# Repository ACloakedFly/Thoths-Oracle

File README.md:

# Thoth's Oracle
## Table of Contents:
- [Features](#Features)
- [Make your own](#Make-your-own)
- [How it works](#How-it-works)
  - [Hardware](#Hardware)
  - [Software](#Software)
  - [Firmware](#Firmware)
- [Configuration](#Configuration)
- [FAQ](#FAQ)
- [Installation](#Installation)
  - [Windows](#Windows)
    - [Launch on startup](#Windows-launch-on-startup)
  - [Linux](#Linux-Tested-on-Ubuntu)
    - [Example](#Example)
    - [GNOME Specific](#GNOME-Specific)
    - [Linux launch on startup](#Linux-launch-on-startup)
    - [Phone Connection](#Phone-connection-to-linux)
- [License](#License)

### USB operated media display/controller for Windows, Linux(, MacOS WIP).

USB music display helps you keep track of what you are listening to without taking up precious screen space. Thoth's Oracle provides a one stop shop for checking on the current media information and basic controls such as skipping tracks, playing and pausing and adjusting the volume.

# Features:

- Software agnostic companion app listens to operating system rather than a specific program like Spotify app or Firefox
  - If OS is aware of media, companion app will be as well
- 320x480 IPS display for maximum readability
- Display the available metadata of current media
  - Thumbnail
  - Title
  - Album
  - Artist
  - Duration and current position
- Basic media control
  - Play/pause
  - Skip track
  - Previous track
  - Mute/unmute
  - Volume control
- Tiltable screen
- Brightness control
- Lightweight companion app (peak RAM usage <80MB, avg <50MB)
- Wallpaper mode to cycle through local images in Wallpaper folder
- Standard components allowing for custom configuration and ease of assembly
  - Hotswappable MX style or Kailh Choc low-profile style switches
  - 6mm rotary potentiometer and encoder
  - 3D printed shell
  - One screw size
  - Small PCB with mostly THT components. Only the hotswap sockets are SMD (hand solderable)

# Make your own!

Everything you need to make your own should be in BOM-and-Assembly. Let me know if anything can be improved.

# How it works:

## Hardware:

- An ESP32-S3 zero controls all of the device inputs and displays information on screen
- ESP32 communicates with PC over USB C OTG connection

## Software:

- The software is written in C# for the Windows App.
- Companion app catches changes to focused media broadcast from the operating system.
- On media change, Thoth requests metadata, packages it, then waits for signal from the Oracle that it is ready to receive the data.
- Metadata is packaged as follows with header tag denoting type, size, etc.:
  - System information containing date and time
  - Media duration and position
  - Media text: title, album, artist
  - Thumbnail
- All text is converted to UTF-8.
- Once ready signal is received, Thoth sends a package over serial port, waits for ready signal, then proceeds to next package.
- When input commands are received, Thoth requests the OS completes the action.

## Firmware:

- The firmware is written in C.
- All serial communications are handled by Core 1. Core 0 handles all display features running LVGL.
- Thoth's Oracle emits ready signal periodically while idling, and emits control commands as soon as they are inputted by the user.
- When data is received, the header tag is analyzed to know which buffer it should be put in.
- If there is an error with the header tag, all subsequent data is dumped, and firmware waits for a pause in data transmission before resetting header information and buffers, and returning to idle state.
- If no errors are detected, data is placed directly into the correct buffer for further analysis in the case of text data, or displayed immediately for images (rolling effect as image loads).
- Media text starts as one big array of characters, and is split into the three fields using escape characters inserted by companion app.
- The font used is DejaVu-Sans in 16 point, with as much of the character set as is hopefully reasonable to ensure maximum language compatibility, without containing the entire set.
- Once the expected number of bytes is received based on the header tag, the header is reset, Oracle emits a ready signal, then enters idle state.
- If firmware times out before receiving expected data, header tag is reset and device enters idle state.

# Configuration:

 The following can be configured from companion app or config file
- Which program to listen to
- Port the device is connected to
- Sensitivity of volume knob
- Which output device to control (default, speakers, headphones, etc.)
- Wallpaper mode

# FAQ:

Someone ask me something, please.

# Installation:

### Windows:

Companion app is provided as portable application that doesn't need installation. Just download and extract the software file for your system wherever you want and run it!

#### Windows launch on startup:
- Right click on .exe and select 'Create shortcut'
- Copy the shortcut to %APPDATA%\Microsoft\Windows\Start Menu\Programs\Startup

### Linux (Tested on Ubuntu):

- Extract folder to desired location.
- Edit .desktop file to match new location if you want app to appear in Apps list.
- Validate and install
```
desktop-file-validate thoths_oracle.desktop
desktop-file-install thoths_oracle.desktop
```
- Check which port Oracle is connected to. It should show up as USB ACM device.
- Verify the device's group permissions are rw and note the group.
- Verify you are part of the group.
- Reboot
#### Example:

```
$ sudo dmesg | grep tty
[    0.139832] printk: legacy console [tty0] enabled
[    6.652489] cdc_acm 1-5.2.2:1.0: ttyACM0: USB ACM device
$ sudo chmod g+rw /dev/ttyACM0
$ ls -ld /dev/ttyACM0
crw-rw---- 1 root dialout 166, 0 Dec  2 18:21 /dev/ttyACM0
$ sudo usermod -a -G dialout dominique
$ sudo reboot
```
#### GNOME Specific:
GNOME may need an extension such as [AppIndicator and KStatusNotifierItem Support](https://extensions.gnome.org/extension/615/appindicator-support/) to display the menu along the top panel. Otherwise, the program will run normally but all settings will have to be changed through the configuration file.

#### Linux launch on startup:
Using Startup Applications Preferences:
-  Add a new entry named Thoths Oracle.
-  If you have installed the .desktop file, set the command to gtk-launch thoths_oracle.desktop
-  Otherwise, change the command to the location you extracted Thoth's Oracle in.
    - eg. /home/dominique/Documents/Programs/Thoths_Oracle_linux/Thoths_Oracle
- Add a comment if desired and save.

#### Phone connection to Linux:
To use audio from phone with all the same features, install [GSConnect](https://github.com/GSConnect/gnome-shell-extension-gsconnect/wiki) for GNOME, or [KDE Connect](https://kdeconnect.kde.org/) for KDE Plasma and follow the instructions to set it up.  
Add kdeconnect or gsconnect to config.yaml in MonitoredProgram section.  
Next, connect phone (source) to Linux (sink) through bluetooth for audio.  
Done!  

# License:

Thoth's Oracle is licensed under GPL-3.0

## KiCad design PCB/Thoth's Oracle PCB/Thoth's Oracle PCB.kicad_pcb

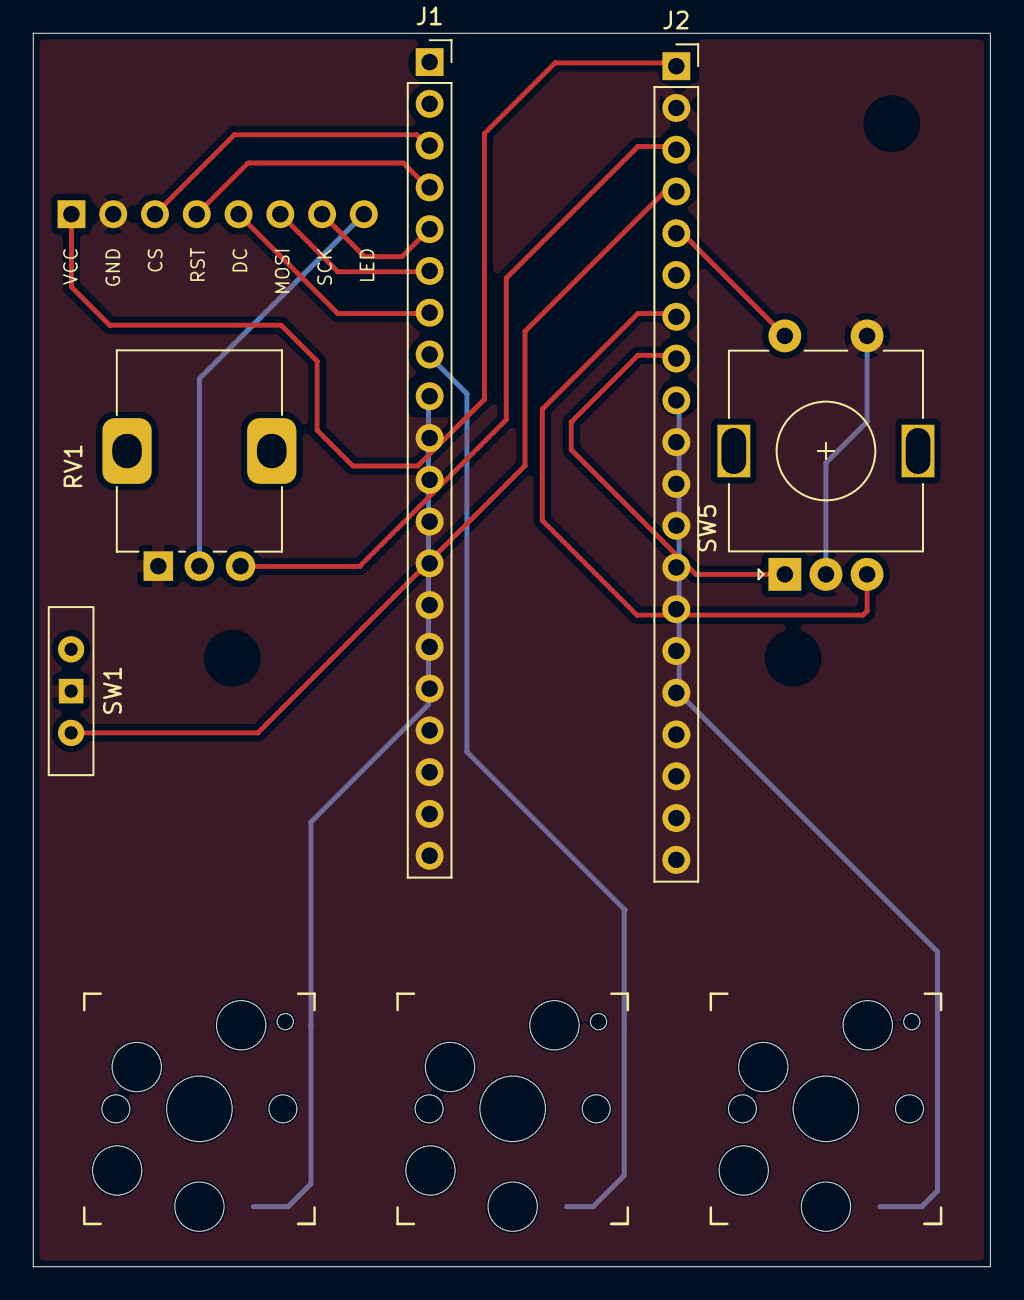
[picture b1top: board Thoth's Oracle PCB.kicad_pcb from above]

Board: 2 copper layers, 58.2 x 75.0 mm, 12 parts (1 on the bottom side), 14 nets.

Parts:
J1: Nano_5v; PinSocket_1x20_P2.54mm_Vertical
J2: Nano_3v3; PinSocket_1x20_P2.54mm_Vertical
J3: Display; PinSocket_1x08_P2.54mm_Horizontal
RV1: R_Potentiometer; Potentiometer_Alps_RK09K_Single_Vertical
SW1: Orientation; SW_Slide-03_Wuerth-WS-SLTV_10x2.5x6.4_P2.54mm
SW2: Prev; Kailh_socket_MX_modified
SW3: Play/Pause; Kailh_socket_MX_modified
SW4: Next; Kailh_socket_MX_modified
SW5: RotaryEncoder_Switch; RotaryEncoder_Alps_EC11E-Switch_Vertical_H20mm
SW6: PP_Alt; Kailh_socket_PG1350_modified
SW7: Prev_Alt; Kailh_socket_PG1350_modified
SW8: Next_Alt; Kailh_socket_PG1350_modified

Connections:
3v3: J1.7, RV1.3
GND: J1.8, J3.2, RV1.1, SW1.1 (B), SW2.2, SW3.2, SW4.2, SW5.C, SW5.S1, SW6.2, SW7.2, SW8.2
LED: J3.8, RV1.2
P1: J1.6, SW1.2 (C)
P2: J1.3, J1.5, SW5.S2
P5: J1.2, SW5.A
P6: J1.1, SW4.1, SW8.1
P7: J2.1, SW2.1, SW7.1
P8: J2.2, SW3.1, SW6.1
P9: J2.3, J3.5
P10: J2.4, J3.6
P11: J2.5, J3.7
P12: J2.6, J3.4
P13: J2.7, J3.3

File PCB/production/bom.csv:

Designator,Footprint,Quantity,Value,LCSC Part #
J1,PinSocket_1x09_P2.54mm_Vertical,1,IO,
J2,PinSocket_1x09_P2.54mm_Vertical,1,MCUDisplay,
J3,PinSocket_1x08_P2.54mm_Vertical,1,Display,
RV1,Potentiometer_Alps_RK09K_Single_Vertical,1,R_Potentiometer,
SW1,SW_Slide-03_Wuerth-WS-SLTV_10x2.5x6.4_P2.54mm,1,Orientation,
SW2,Kailh_socket_MX_PG1350,1,Prev,
SW3,Kailh_socket_MX_PG1350,1,Play/Pause,
SW4,Kailh_socket_MX_PG1350,1,Next,
SW5,RotaryEncoder_Alps_EC11E-Switch_Vertical_H20mm,1,RotaryEncoder_Switch,

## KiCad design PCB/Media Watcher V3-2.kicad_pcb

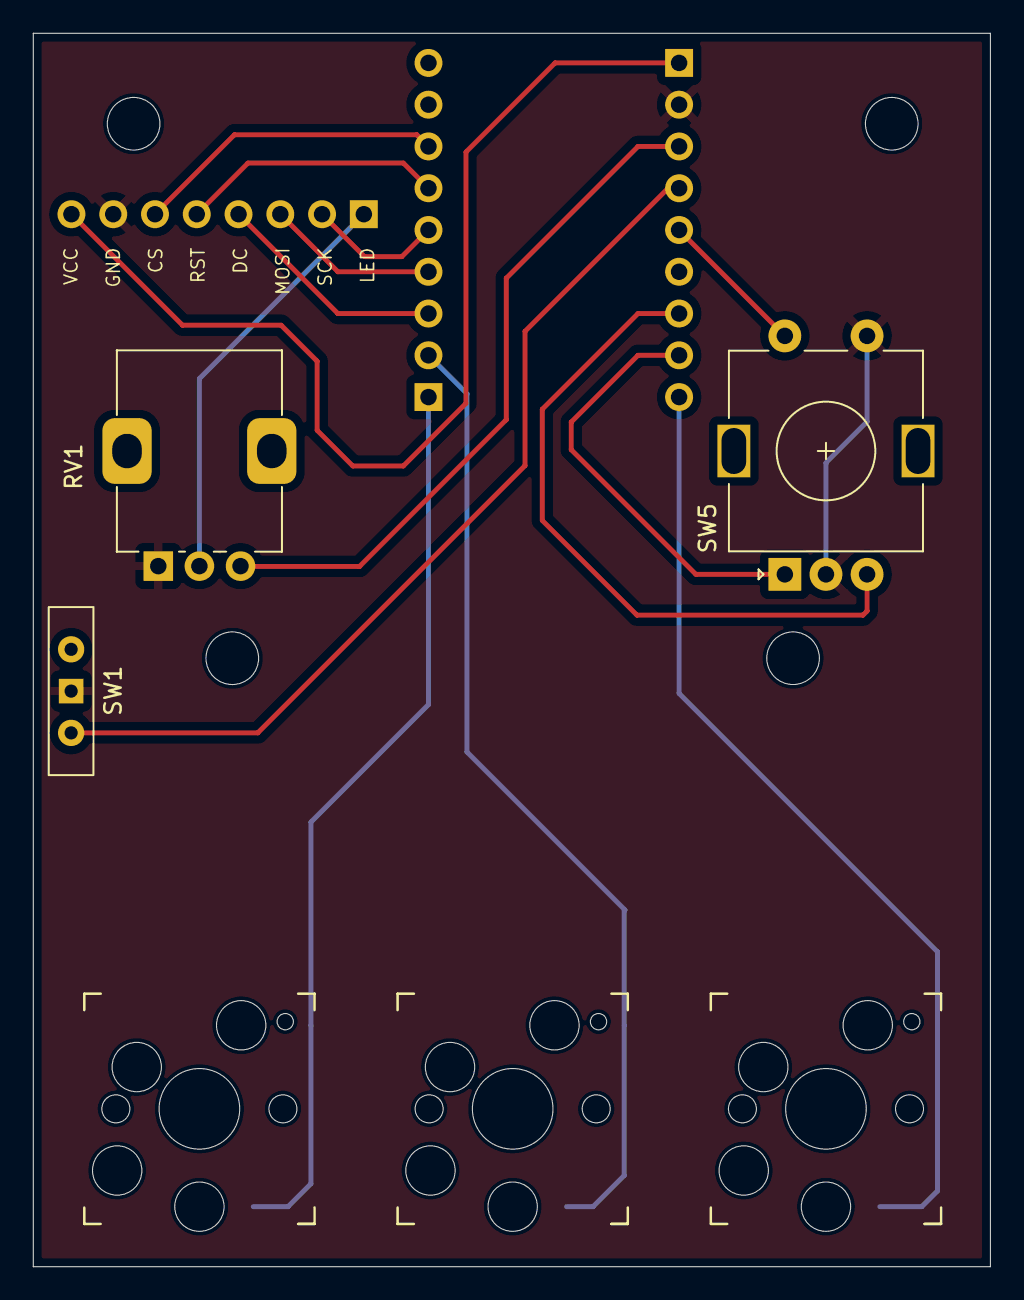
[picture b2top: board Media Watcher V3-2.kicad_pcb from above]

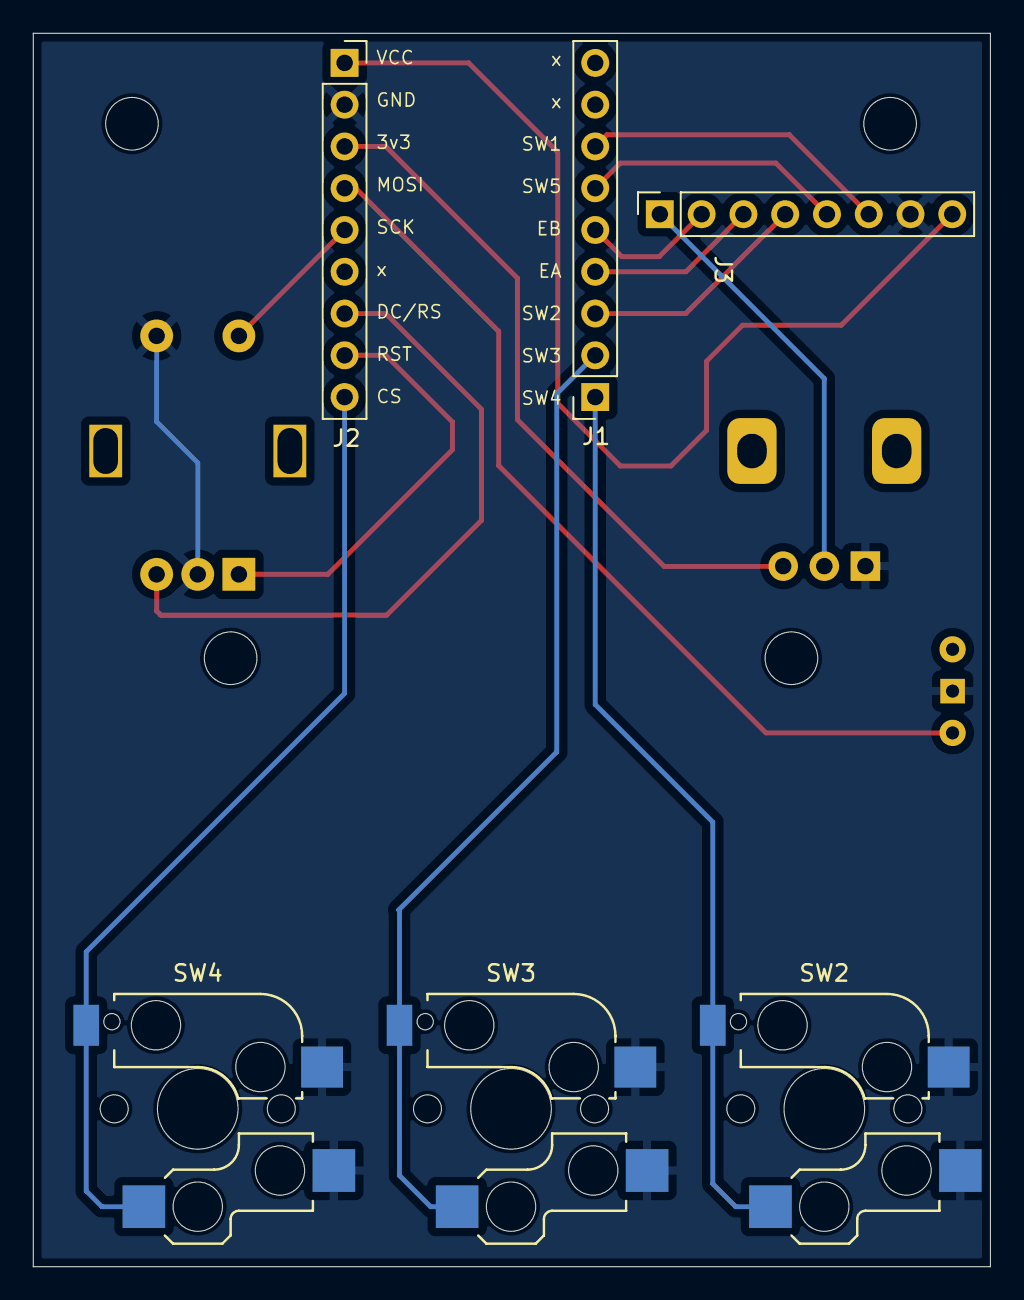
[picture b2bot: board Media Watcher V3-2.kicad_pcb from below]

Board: 2 copper layers, 58.2 x 75.0 mm, 9 parts (3 on the bottom side), 16 nets.

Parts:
J1: IO; PinSocket_1x09_P2.54mm_Vertical
J2: MCUDisplay; PinSocket_1x09_P2.54mm_Vertical
J3: Display; PinSocket_1x08_P2.54mm_Vertical
RV1: R_Potentiometer; Potentiometer_Alps_RK09K_Single_Vertical
SW1: Orientation; SW_Slide-03_Wuerth-WS-SLTV_10x2.5x6.4_P2.54mm
SW2: Prev; Kailh_socket_MX_PG1350
SW3: Play/Pause; Kailh_socket_MX_PG1350
SW4: Next; Kailh_socket_MX_PG1350
SW5: RotaryEncoder_Switch; RotaryEncoder_Alps_EC11E-Switch_Vertical_H20mm

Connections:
3v3: J2.3, RV1.3
+5V: J2.1, J3.8
GND: J2.2, J3.7, RV1.1, SW1.1 (B), SW2.2, SW3.2, SW4.2, SW5.C, SW5.S1
LED: J3.1, RV1.2
P1: J2.4, SW1.2 (C)
P2: J2.5, SW5.S2
P4: J2.7, SW5.B
P5: J2.8, SW5.A
P6: J2.9, SW4.1
P7: J1.1, SW2.1
P8: J1.2, SW3.1
P9: J1.3, J3.4
P10: J1.4, J3.3
P11: J1.5, J3.2
P12: J1.6, J3.5
P13: J1.7, J3.6

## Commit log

2025-07-03 Inital
2025-07-03 Initial 1
2025-07-04 Restructure
2025-07-09 Added PCB and 3d models
2025-07-09 Rename PCB Assembly Instructions.md to README.md
2025-07-09 Rename README to README.md
2025-07-09 Added Software
2025-07-11 Big updates
2025-07-13 Added documentation
2025-07-13 Finished documentation and cleaned up code
2025-07-13 Added firmware README
2025-07-14 Further cleaning
2025-07-14 Cleaning
2025-07-16 Changed messages to separate idling and finished
2025-07-16 Cleaned up code Added YAML file Proper connect/reconnect/disconnect behaviour
2025-07-16 Added classes for communication codes
2025-07-16 UI works with serial comms
2025-07-16 Adding configuration support
2025-07-16 More config stuff
2025-07-16 Added Timers for DeviceHandler loop
2025-07-17 Cleaned up UI
2025-07-18 Finaliozed
2025-07-18 Smol
2025-07-18 untracked builds folder
2025-07-18 Untracked builds/ folder
2025-07-18 Lgos and icons
2025-07-19 Customized UI
2025-07-20 Finalized Software
2025-07-20 Finalized
2025-07-20 Fixed GSMTCS bug on initial connection without a config file
2025-07-20 Increased default mediacheck time for better responsiveness
2025-07-20 Reintroduced delay between retrieving thumbnail and resizing to ensure it is updated before resizing
2025-07-20 Preparing for release
2025-07-20 Added image of Oracle
2025-07-20 Added image of the Oracle
2025-07-22 Cleaned new declarations
2025-07-23 Added priority to MonitoredProgram and moved it to sessionschanged rather than currentsessionchanged. Updated config to reflect this. Added copyright and version number to exe. If program is firefox,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
2025-07-23 Tiny cleanup
2025-07-23 Added retry if image has not been received yet instead of just returning unsuccessfully
2025-07-24 Added product images
2025-07-24 Cleaned board
2025-07-24 Cleaned shell
2025-07-24 Rename BOM.md to BOM-and-Assembly.md
2025-07-24 Cleaned stl
2025-07-24 Fixed thumbscrew orientation
2025-07-24 Added support setting
2025-07-25 Added queue for media writing thread to let other threads send messages. Fixed a problem with the default config causing errors on first startup
2025-07-25 Removed unnecessary using
2025-07-26 Reworked Reading and removed a bunch of async calls Fixed configuration files not loading correctly
2025-07-26 Fixed issues with config
2025-07-27 Added build pictures and updated inputs plate
2025-07-27 Added a couple more Assembly_Pics
2025-07-28 Removed some metadata from images
2025-08-08 Separated hotswap sockets with modified footprints so they don't overlap. Typo in assembly
2025-09-16 Configuration file fixed to actually update correct values and not the non-ui from ui csproj updated for true single file publishing
2025-09-16 added more characters
2025-09-18 Added better support for Windows 11
2025-09-30 Added flag to check duration, if duration set, only update play status
2025-10-10 Moved windows software files into dedicated folder in perparation of other operating systems
2025-10-10 Added linux Software
2025-10-10 Fixed some possible null dereferences and icon file path Updated to Windows 11 .net8.0 minimum target, still works on Windows 10
2025-10-15 Added ui and added licence
2025-10-15 Added spec and example desktop file
2025-12-02 Update README.md
    Added installation instructions for Linux (Ubuntu)
2025-12-02 Update README.md
    Added startup launch instructions
2025-12-08 Added LittleFS
2025-12-11 Testing new gif feature
2025-12-14 Update README.md
    typo
2026-01-05 Fix for Windows losing connection when asleep or off
2026-01-05 Upgraded Magick.Net version to latest patch
2026-01-09 Stableish gif!
2026-01-10 Seems to work with octal flash chip with minimal tearing
2026-01-11 Updated requirements
2026-01-13 Fixed the last fix for handling sleep. Last attempt incorrectly used the serial exception handler. New fix uses the mediacheck function to repoll the current media session. Also fixed bug with the co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
2026-01-13 Small fixes for initial config handling
2026-01-21 Added more context to input logging, added automatically checking for icons in parent folder rather than changing between testing and "production", Removide subdirectory checking in ConfigHandler, th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
2026-01-22 Added spam protection on config changes App now warns if selected device is not found Fixed small issue with Default Device seemingly being selected if selected device is not found (until something i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
2026-01-22 Now checks if currently selected playback device is default when config set to Default Device. If not default, get new default.
2026-01-22 Updated csproj for easier publishing
2026-02-03 Updated time handling for proper time
2026-02-04 Only makes time on minute change rather than every second which was causing time drift
2026-02-09 Added exception hanlder to inputs from device Tweaked default config to have common apps watched by default
2026-02-16 Big changes to linux. Increased stability, added automatic session handling, fixed occasional playback status not being updated
2026-02-16 Updated requirements.txt
2026-02-16 Added shortcut to folder for ease of use Added x11 as backend in .desktop file because it seems to not work otherwise Refactored session watching. It could probably use more work to simplify it, but 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
2026-02-16 Update README.md
    Updated startup command instructions for linux
2026-02-18 Added live colour changing to Firmware Added very basic colour changing in Linux software. Right now it is just through the config file, but the plan is a colour picker in the tray icon. This doesn't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
2026-02-22 Fixed sleep causing infinite loop of writing to disk (very not cool) Added file size check to log to not exceed MAX_LOG_SIZE (set to 200 mb for now, probably way too big for production, but good for 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
2026-02-26 More stability improvements, reworked uri handling
2026-03-15 Added better mpris:artUrl handling
2026-03-15 Reduced max log file size to 20 mb
2026-03-16 Added disconnect and reconnect handling. Tweaked media check
2026-03-16 Updated exit handling. Much less hanging around past its welcome.
2026-03-16 Wait do I even need to join every thread?
2026-04-12 Update README.md
    Added TOC, basic instructions for bluetooth audio
2026-05-05 many things changed a while ago
2026-05-08 Working on gif capabilites with 8-bit parallel display instead of SPI
2026-05-09 Update README.md
    Added GNOME specific configuration instructions
2026-05-09 Fixed wallpaper text bug and added error handler
2026-06-18 Working on proper RGB support

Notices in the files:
PCB/Thoth's Oracle PCB/Thoth's Oracle PCB.kicad_pcb:
Copyright (C) Dominique Negm 2025
